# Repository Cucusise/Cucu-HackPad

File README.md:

# Cucu's HackPad Project

## 1. Introduction
This is my first project and it's a hackpad designed to enhance my skills, not only in design but also in manual dexterity.
It includes the electrical schematic, PCB layout, and the 3D printed case for assembly.

### Overview

---

## 2. Schematic Part
The electrical schematic was designed in KiCad and shows all connections between components.
Thanks to the tutorial I gained the knowledge to design this scheme.
It clearly illustrates how the microcontroller, switches, and other peripherals are connected.

### Scheme

---

## 3. PCB Layout Part
The PCB layout optimizes space and minimizes interference.  
It includes clean routing and logical component placement.

### Layout

### 3D Layout

---

## 4. Case and Assembly part
The case is designed to fit the PCB and components perfectly.  
It ensures everything is protected and accessible for assembly.

### Screenshot

---

## 5. BOM

| Qty | Part | Extra Info |
|-----|------|------------|
| 1   | Case Print | |
| 1   | Seeed XIAO RP2040 | |
| 4   | MX-Style Switches | |
| 4   | Blank DSA Keycaps | |
| 8   | M3x16mm Screws | |
| 8   | M3x5mm x 4mm Heatset Inserts | |
| 1   | SSD1306 | [Useful Link](https://shorturl.at/LtIs5) |

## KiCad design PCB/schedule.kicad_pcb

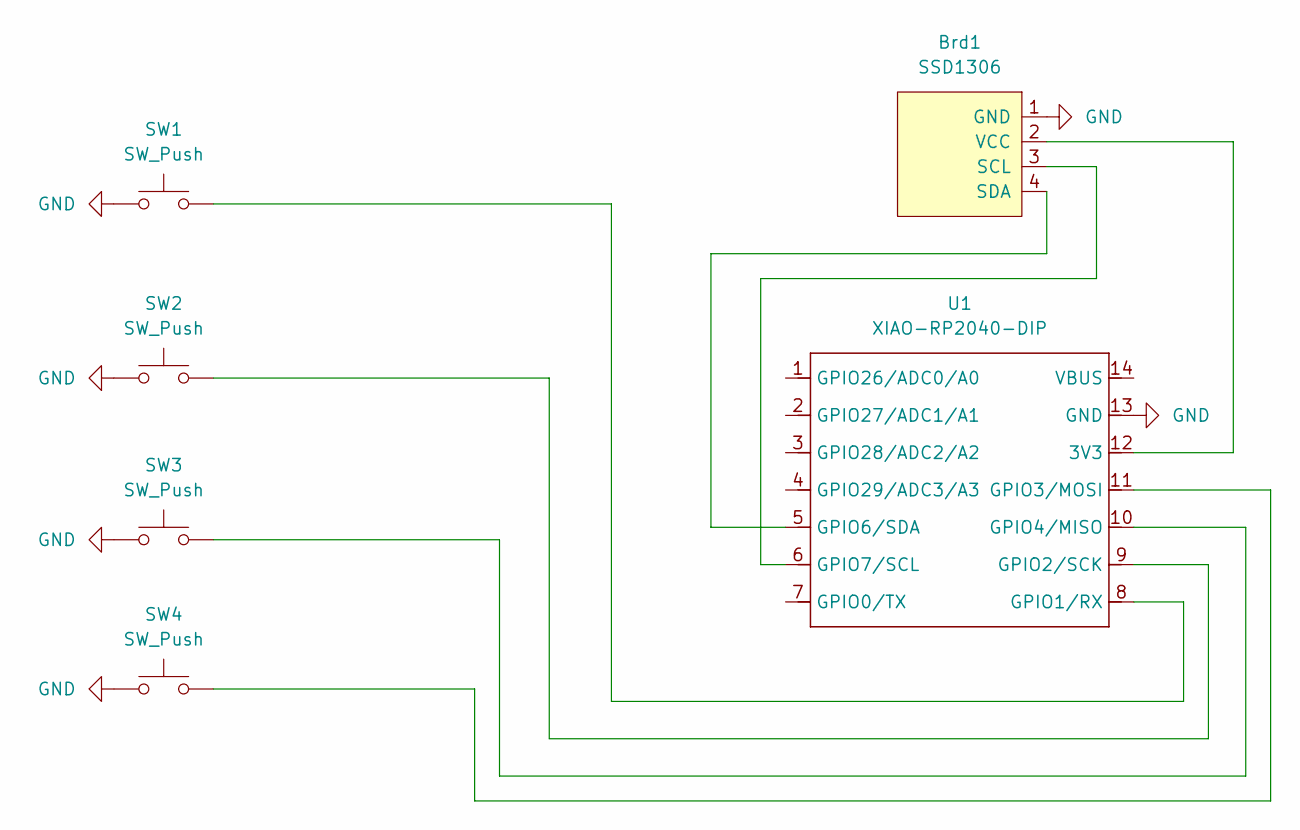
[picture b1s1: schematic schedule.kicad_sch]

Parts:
Brd1: SSD1306; Adafruit_SSD1306
SW1, SW2, SW3, SW4: SW_Push; SW_Cherry_MX_1.00u_PCB
U1: XIAO-RP2040-DIP

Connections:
GND: Brd1.1 (GND), SW1.1, SW2.1, SW3.1, SW4.1, U1.13 (GND)
unnamed: Brd1.3 (SCL), U1.6 (GPIO7/SCL)
unnamed: Brd1.4 (SDA), U1.5 (GPIO6/SDA)
unnamed: Brd1.2 (VCC), U1.12 (3V3)
unnamed: SW1.2, U1.8 (GPIO1/RX)
unnamed: SW2.2, U1.9 (GPIO2/SCK)
unnamed: SW4.2, U1.11 (GPIO3/MOSI)
unnamed: SW3.2, U1.10 (GPIO4/MISO)

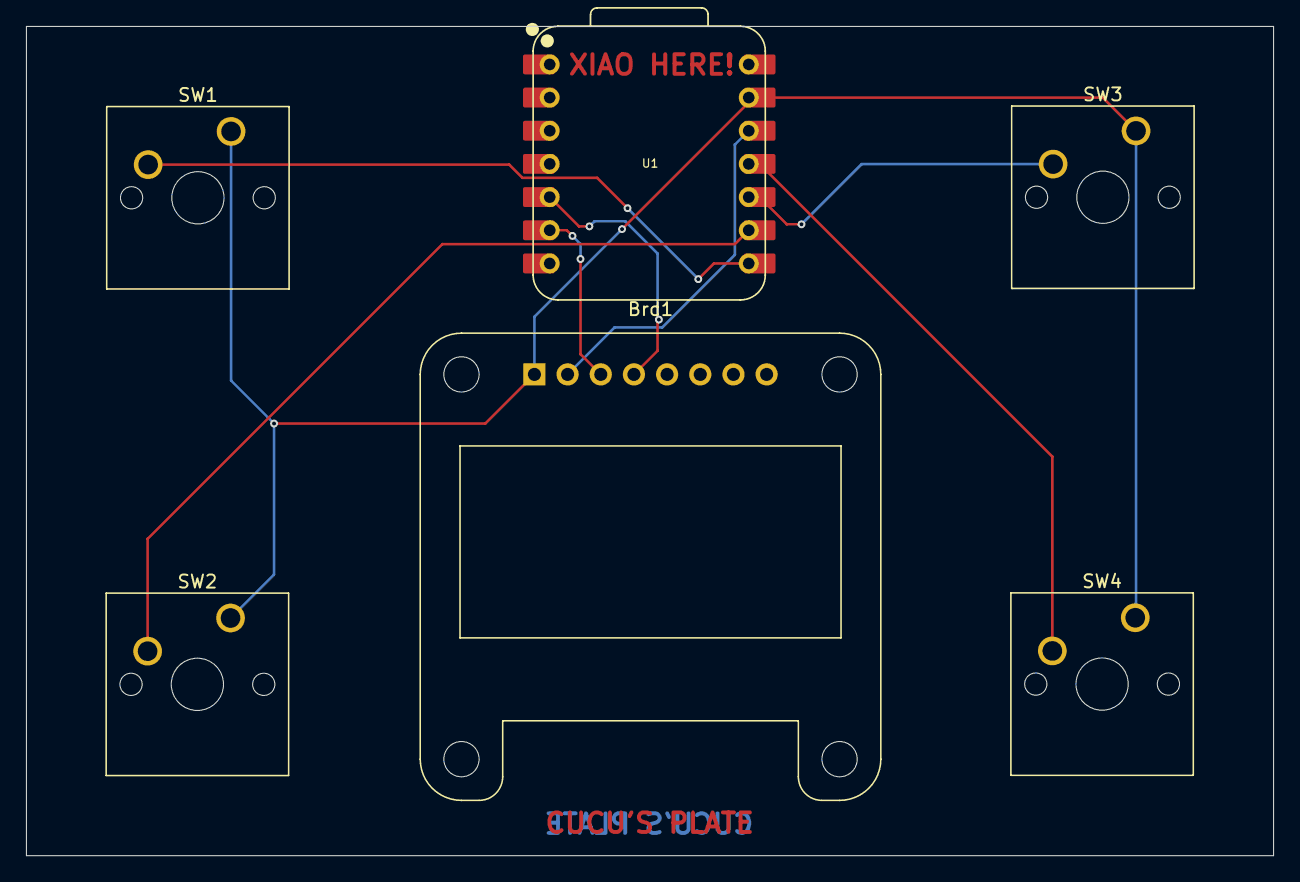
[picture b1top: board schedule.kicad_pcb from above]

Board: 2 copper layers, 95.5 x 63.5 mm, 6 parts (0 on the bottom side), 8 nets.

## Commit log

2025-12-22 Ready to submit!
2025-12-22 test
2025-12-22 Read me & Ready to Submit!
2025-12-24 Remodelation
2025-12-24 Extra OLED info
2025-12-24 Shorter link
2025-12-24 Shorter Link correction
